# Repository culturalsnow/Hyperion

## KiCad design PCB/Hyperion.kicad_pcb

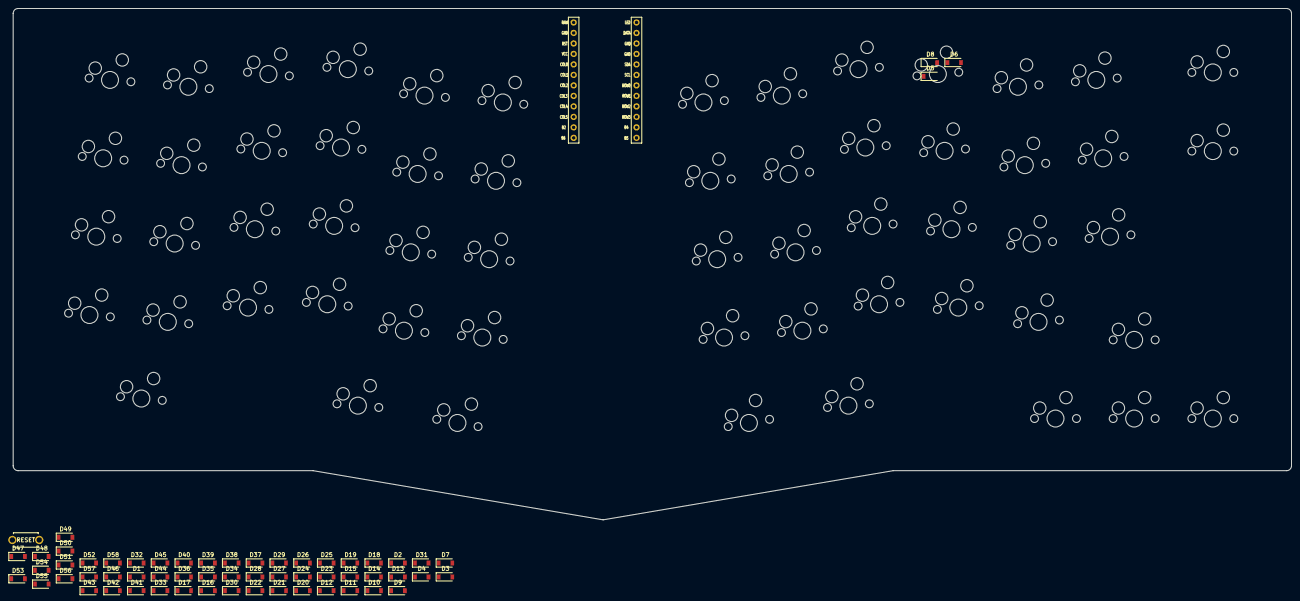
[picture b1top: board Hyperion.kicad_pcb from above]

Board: 2 copper layers, 309.6 x 123.8 mm, 118 parts (0 on the bottom side), 78 nets, no tracks yet.

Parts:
D1, D2, D3, D4, D5, D6, D7, D8, D9, D10, D11, D12, D13, D14, D15, D16, D17, D18, D19, D20, D21, D22, D23, D24, D25, D26, D27, D28, D29, D30, D31, D32, D33, D34, D35, D36, D37, D38, D39, D40, D41, D42, D43, D44, D45, D46, D47, D48, D49, D50, D51, D52, D53, D54, D55, D56, D57, D58: 1N4148; D_SOD-123
SW1, SW2, SW3, SW4, SW5, SW6, SW7, SW8, SW9, SW10, SW11, SW12, SW13, SW14, SW15, SW16, SW17, SW18, SW19, SW20, SW21, SW22, SW23, SW24, SW25, SW26, SW27, SW28, SW29, SW30, SW31, SW32, SW33, SW34, SW35, SW36, SW37, SW38, SW39, SW40, SW41, SW42, SW43, SW44, SW45, SW46, SW47, SW48, SW49, SW50, SW51, SW52, SW53, SW54, SW55, SW56, SW57, SW58: SW_PUSH; CherryMX_Hotswap_Back
SW59: SW_PUSH; ResetSW
U1: ProMicro; ProMicro_v2_Backside

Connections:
GND: SW59.2, U1.3, U1.4, U1.23
unnamed: D1.2, SW1.2
unnamed: D2.2, SW2.2
unnamed: D3.2, SW3.2
unnamed: D4.2, SW4.2
unnamed: D5.2, SW5.2
unnamed: D6.2, SW6.2
unnamed: D7.2, SW7.2
unnamed: D8.2, SW8.2
unnamed: D9.2, SW9.2
unnamed: D10.2, SW10.2
unnamed: D11.2, SW11.2
unnamed: D12.2, SW12.2
unnamed: D13.2, SW13.2
unnamed: D14.2, SW14.2
unnamed: D15.2, SW15.2
unnamed: D16.2, SW16.2
unnamed: D17.2, SW17.2
unnamed: D18.2, SW18.2
unnamed: D19.2, SW19.2
unnamed: D20.2, SW20.2
unnamed: D21.2, SW21.2
unnamed: D22.2, SW22.2
unnamed: D23.2, SW23.2
unnamed: D24.2, SW24.2
unnamed: D25.2, SW25.2
unnamed: D26.2, SW26.2
unnamed: D27.2, SW27.2
unnamed: D28.2, SW28.2
unnamed: D29.2, SW29.2
unnamed: D30.2, SW30.2
unnamed: D31.2, SW31.2
unnamed: D32.2, SW32.2
unnamed: D33.2, SW33.2
unnamed: D34.2, SW34.2
unnamed: D35.2, SW35.2
unnamed: D36.2, SW36.2
unnamed: D37.2, SW37.2
unnamed: D38.2, SW38.2
unnamed: D39.2, SW39.2
unnamed: D40.2, SW40.2
unnamed: D41.2, SW41.2
unnamed: D42.2, SW42.2
unnamed: D43.2, SW43.2
unnamed: D44.2, SW44.2
unnamed: D45.2, SW45.2
unnamed: D46.2, SW46.2
unnamed: D47.2, SW47.2
unnamed: D48.2, SW48.2
unnamed: D49.2, SW49.2
unnamed: D50.2, SW50.2
unnamed: D51.2, SW51.2
unnamed: D52.2, SW52.2
unnamed: D53.2, SW53.2
unnamed: D54.2, SW54.2
unnamed: D55.2, SW55.2
unnamed: D56.2, SW56.2
unnamed: D57.2, SW57.2
unnamed: D58.2, SW58.2
col0: SW1.1, SW2.1, SW3.1, SW4.1, U1.9
col1: SW5.1, SW6.1, SW7.1, SW8.1, SW9.1, U1.8
col2: SW10.1, SW11.1, SW12.1, SW13.1, U1.7
col3: SW14.1, SW15.1, SW16.1, SW17.1, U1.6
col4: SW18.1, SW19.1, SW20.1, SW21.1, SW22.1, U1.5
col5: SW23.1, SW24.1, SW25.1, SW26.1, SW27.1, U1.2
col6: SW28.1, SW29.1, SW30.1, SW31.1, SW32.1, U1.1
col7: SW33.1, SW34.1, SW35.1, SW36.1, SW37.1, U1.15
col8: SW38.1, SW39.1, SW40.1, SW41.1, U1.16
col9: SW42.1, SW43.1, SW44.1, SW45.1, U1.17
col10: SW46.1, SW47.1, SW48.1, SW49.1, SW50.1, U1.18
col11: SW51.1, SW52.1, SW53.1, SW54.1, SW55.1, U1.19
col12: SW56.1, SW57.1, SW58.1, U1.20
reset: SW59.1, U1.22
row0: D1.1, D5.1, D10.1, D14.1, D18.1, D23.1, D28.1, D33.1, D38.1, D42.1, D46.1, D51.1, D56.1, U1.10
row1: D2.1, D6.1, D11.1, D15.1, D19.1, D24.1, D29.1, D34.1, D39.1, D43.1, D47.1, D52.1, D57.1, U1.14
row2: D3.1, D7.1, D12.1, D16.1, D20.1, D25.1, D30.1, D35.1, D40.1, D44.1, D48.1, D53.1, U1.11
row3: D4.1, D8.1, D13.1, D17.1, D21.1, D26.1, D31.1, D36.1, D41.1, D45.1, D49.1, D54.1, U1.12
row4: D9.1, D22.1, D27.1, D32.1, D37.1, D50.1, D55.1, D58.1, U1.13

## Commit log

2019-10-27 pcb almost dome
2019-10-31 pcb first draft
2019-11-06 outlined
